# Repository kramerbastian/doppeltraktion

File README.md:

# *doppeltraktion*

Doppeltraktion (German for double heading — that's when two locomotives pull together on a train) is the world's most intuitive model railway throttle. It has ≈6x fewer buttons and switches than market competitors, such as the Uhlenbrock Intellibox II. It connects to your model railroad using LCC or to your computer via USB to control software such as RocRail or JMRI*¹ and can control two locomotives simultaneously. <br>
<sub>*¹ not yet implemented</sub>

### Functions

### What is LCC?

LCC is a relatively new standard by the NMRA to control devices using a CAN bus. It's completely free and open-source, unlike alternatives like LocoNet, which comes with a pretty hefty licensing fee for device manufacturers.

### Motivation

I've been building on my model railway from an early age. As time progressed, the electronics and operations became so complicated that nobody else could really control it. That's why I always wanted to build a physical throttle that's not dependent on external computers or phones. Everything should be ready to use when you turn on the power. Of course, there are alternatives from big manufacturers, such as the mentioned Intellibox or the ESU ECoS, but these devices are very expensive (500€+) and aren't compatible with my DIY DCCEX base station.

### Design

It might seem a bit unusual to have five PCBs for this relatively small project, but to keep PCB costs low (by being under 100x100mm), I decided to split the covers (aluminum PCBs) and those boards where the switches, LEDs, and potentiometers mount. The PCBs on the side are identical. Everything is connected to a custom, small control board, which houses the ESP32 as well as all the CAN circuitry (for LCC).

By also splitting the base into two parts, everything should fit on the 180x180mm build plate of the A1 mini.

The plates (that‘s where the switches mount mechanically) use a sandwich design (top plate - bottom plate - PCB) to avoid having to use supports and ensure dimensional accuracy for mounting the switches.

I couldn’t find a good CAD model or accurate dimensions for the 16mm selector knob, so there’s a hole in the cover and the plates beneath it. The cutout size should be correct. I just need to verify the depth and maybe adjust the top side plate once the switch arrives.

#### Designed Parts

| Name                                                  | Image                                                                                                                                     | File                                                  | Quantity  |
|-------------------------------------------------------|-------------------------------------------------------------------------------------------------------------------------------------------|-------------------------------------------------------|-----------|
| Top center plate                                      |          | [STL](./production/3d/top_center_plate.stl)           | 1         |
| Bottom center plate                                   |    | [STL](./production/3d/bottom_center_plate.stl)        | 1         |
| Top side plate                                        |              | [STL](./production/3d/top_side_plate.stl)             | 2         |
| Bottom side plate                                     |        | [STL](./production/3d/bottom_side_plate.stl)          | 2         |
| Top left base                                         |                | [STL](./production/3d/top_base_left.stl.stl)          | 1         |
| Top right base                                        |             | [STL](./production/3d/top_base_right.stl)             | 1         |
| Bottom left base                                      |          | [STL](./production/3d/bottom_base_left.stl.stl)       | 1         |
| Bottom right base                                     |           | [STL](./production/3d/bottom_base_right.stl)          | 1         |
| Bottom cover                                          |             | [STL](./production/3d/bottom_cover.stl)               | 2         |
| Light guide <br> (print the last layer in white PLA)  |               | [STL](./production/3d/light_guide.stl)          | 7         |
| Knob                                                  |                      | [STL](./production/3d/knob.stl)                    | 1         |
| Mounting PCB side                                     |         | [Gerber](./production/pcbs/side.zip)                  | 2         |
| Mounting PCB center                                   |       | [Gerber](./production/pcbs/center.zip)                | 1         |
| Control PCB                                           |               | [Gerber](./production/pcbs/control.zip)               | 1         |
| Center cover                                          |              | [Gerber](./production/pcbs/cover_center.zip)          | 1         |
| Side cover                                            |                | [Gerber](./production/pcbs/cover_side.zip)            | 2         |

### Assembly

1. Print all necessary parts: 2x [top side plate](./production/3d/top_side_plate.stl), 2x [bottom side plate](./production/3d/bottom_side_plate.stl), 1x [top center plate](./production/3d/top_center_plate.stl), 1x [bottom center plate](./production/3d/bottom_center_plate.stl), 1x [top left base](./production/3d/top_base_left.stl), 1x [top right base](./production/3d/top_base_right.stl), 1x [bottom left base](./production/3d/bottom_base_left.stl), 1x [bottom right base](./production/3d/bottom_base_right.stl), 1x [bottom left cover](./production/3d/bottom_cover_left.stl), 1x [bottom right cover](./production/3d/bottom_cover_right.stl). (I know these names are awful, but I couldn‘t come up with better ones.)

2. Insert the heat-set inserts into their respective holes.

3. Mount all the PCBs and solder the switches in place.

4. You can now secure the plates onto the top base. With the control board mounted on the bottom base, it can also be secured to the top base.

5. Now is the time to run the wires from the modules (2x side, 1x center) and the display to the control board. Also, wire up the selector knob to the WAGO terminals and ground.

6. The final step is to screw both the top cover (the aluminium one) and the bottom cover onto the construction.

### BOM

|Part                     |Manufacturer               |Product                             |Quantity|Price each|Total Price|Link                                                                                                                                            |
|-------------------------|---------------------------|------------------------------------|--------|----------|-----------|------------------------------------------------------------------------------------------------------------------------------------------------|
|Inserts                  |YMAX                       |Brass Threaded Insert Nut Kit       |1       | $1.460   | $1.46     | [Link](https://www.aliexpress.com/item/1005006472962973.html)                                                                                  |
|Display                  |EstarDyn                   |12864-06D                           |1       | $6.250   | $6.25     |[Link](https://www.aliexpress.com/item/1005006160620381.html)                                                                                   |
|Rotary Knob              |Sweideer                   |LA-155C                             |1       | $2.630   | $2.63     |[Link](https://www.aliexpress.com/item/1005007495183351.html)                                                                                   |
|Switches                 |-                          |10 Pieces Keyboard Replacement Parts|1       | $1.590   | $1.59     |[Link](https://www.aliexpress.com/item/1005004341695529.html)                                                                                   |
|Keycaps                  |-                          |B0KA 20PCs PBT Blank                |1       | $4.470   | $4.47     |[Link](https://www.aliexpress.com/item/1005004525231272.html)                                                                                   |
|M2x5 12x                 |SCREWHOME                  |50pcs M2x5mm ULTRATHIN              |1       | $1.460   | $1.46     |[Link](https://www.aliexpress.com/item/1005005070119421.html)                                                                                   |
|M2x10 4x                 |LIYA                       |50pcs M2x10mm                       |1       | $1.560   | $1.56     |[Link](https://www.aliexpress.com/item/32810872544.html)                                                                                        |
|M3x20 2x                 |LIYA                       |50pcs M3x20mm                       |1       | $2.760   | $2.76     |[Link](https://www.aliexpress.com/item/32810872544.html)                                                                                        |
|M3x8 8x                  |LIYA                       |50pcs M3x8mm                        |1       | $1.730   | $1.73     |[Link](https://www.aliexpress.com/item/32810872544.html)                                                                                        |
|M3x8 Countersunk 8x      |ZONST                      |50pcs M3x8mm Countersunk            |1       | $1.810   | $1.81     |[Link](https://www.aliexpress.com/item/1005002333132596.html)                                                                                   |
|M3x12 12x                |LIYA                       |50pcs M3x12mm                       |1       | $2.060   | $2.06     |[Link](https://www.aliexpress.com/item/32810872544.html)                                                                                        |
|M3x10 5x                 |LIYA                       |50pcs M3x10mm                       |1       | $1.940   | $1.94     |[Link](https://www.aliexpress.com/item/32810872544.html)                                                                                        |
|ESP32-S3                 |EXPRESSIF                  |ESP32-S3-WROOM-1U-N16R2             |1       | $5.660   | $5.66     |[Link](https://lcsc.com/product-detail/WiFi-Modules_ESPRESSIF-ESP32-S3-WROOM-1U-N16R8_C3013946.html)                                            |
|LDO                      |Advanced Monolithic Systems|AMS1117-3.3                         |5       | $0.170   | $0.85     |[Link](https://lcsc.com/product-detail/Voltage-Regulators-Linear-Low-Drop-Out-LDO-Regulators_Advanced-Monolithic-Systems-AMS1117-3-3_C6186.html)|
|CAN transceiver          |NXP                        |TJA1051T,118                        |1       | $0.960   | $0.96     |[Link](https://lcsc.com/product-detail/CAN-Transceivers_NXP-TJA1051T-118_C18387.html)                                                           |
|I/O expander             |HGSEMI                     |PCF8574T/TR                         |1       | $0.790   | $0.79     |[Link](https://lcsc.com/product-detail/I-O-Expanders_HGSEMI-PCF8574T-TR_C2987288.html)                                                          |
|4 pin connector          |JST                        |B4B-PH-K-S(LF)(SN)                  |10      | $0.041   | $0.41     |[Link](https://lcsc.com/product-detail/Wire-To-Board-Connector_JST-B4B-PH-K-S-LF-SN_C131334.html)                                               |
|6 pin connector          |JST                        |B6B-PH-K-S(LF)(SN)                  |10      | $0.067   | $0.67     |[Link](https://lcsc.com/product-detail/Wire-To-Board-Connector_JST-B6B-PH-K-S-LF-SN_C131342.html)                                               |
|9 pin connector          |JST                        |B9B-PH-K-S(LF)(SN)                  |5       | $0.051   | $0.26     |[Link](https://lcsc.com/product-detail/Wire-To-Board-Connector_JST-B9B-PH-K-S-LF-SN_C157968.html)                                               |
|4 pin connector housing  |JST                        |PHR-4                               |50      | $0.016   | $0.79     |[Link](https://lcsc.com/product-detail/Housings-Wire-To-Board-Wire-To-Wire_JST-PHR-4_C111514.html)                                              |
|6 pin connector housing  |JST                        |PHR-6                               |20      | $0.020   | $0.40     |[Link](https://lcsc.com/product-detail/Housings-Wire-To-Board-Wire-To-Wire_JST-PHR-6_C157952.html)                                              |
|9 pin connector housing  |JST                        |PHR-9                               |20      | $0.036   | $0.72     |[Link](https://lcsc.com/product-detail/Housings-Wire-To-Board-Wire-To-Wire_JST-PHR-9_C157949.html)                                              |
|Connector contact        |JST                        |SPH-002T-P0.5S                      |100     | $0.008   | $0.80     |[Link](https://lcsc.com/product-detail/Housing-Contact_JST-SPH-002T-P0-5S_C111515.html)                                                         |
|USB-B port               |TE Connectivity            |292304-1                            |1       | $0.470   | $0.47     |[Link](https://lcsc.com/product-detail/USB-Connectors_TE-Connectivity-292304-1_C86462.html)                                                     |
|100uF capacitors         |Rubycon                    |35ZLH100MEFC6.3X11                  |10      | $0.059   | $0.59     |[Link](https://lcsc.com/product-detail/Aluminum-Electrolytic-Capacitors-Leaded_Rubycon-35ZLH100MEFC6-3X11_C109392.html)                         |
|100nF capacitors         |Samsung Electro-Mechanics  |CL31B104KBCNNNC                     |20      | $0.137   | $2.74     |[Link](https://lcsc.com/product-detail/Multilayer-Ceramic-Capacitors-MLCC-SMD-SMT_Samsung-Electro-Mechanics-CL31B104KBCNNNC_C24497.html)        |
|10kOhm resistors         |YAGEO                      |RC1206FR-0710KL                     |100     | $0.004   | $0.37     |[Link](https://lcsc.com/product-detail/Chip-Resistor-Surface-Mount_YAGEO-RC1206FR-0710KL_C132649.html)                                          |
|Sliding potentiometers   |ALPSALPINE                 |RS6011YA600M                        |2       | $1.451   | $2.90     |[Link](https://lcsc.com/product-detail/Potentiometers-Variable-Resistors_ALPSALPINE-RS6011YA600M_C470623.html)                                  |
|RGB LEDs                 |XINGLIGHT                  |XL-5050RGBC-WS2812B                 |20      | $0.049   | $0.98     |[Link](https://lcsc.com/product-detail/RGB-LEDs-Built-in-IC_XINGLIGHT-XL-5050RGBC-WS2812B_C2843785.html)                                        |
|RJ45 port - existing     |Phoenix Contact            |1337243                             |2       | -        | -         |[Link](https://www.phoenixcontact.com/en-pc/products/rj45-pcb-connectors-cuc-sp-j1st-a-r4lt-thr-led-1337243)                                    |
|WAGO terminals - existing|WAGO                       |2601-3105                           |2       | -        | -         |[Link](https://www.wago.com/de/leiterplattenanschluss/leiterplattenklemme/p/2601-3105)                                                          |
|Slide switch - existing  |XKB Connection             |SS13E05L2                           |1       | -        | -         |[Link](https://lcsc.com/product-detail/Slide-Switches_XKB-Connection-SS13E05L2_C2884809.html)                                                   |
|Control PCB              |JLCPCB                     |5x FR4 PCB                          |1       | $1.720   | $1.72     |                                                                                                                                                |
|Side PCB                 |JLCPCB                     |5x FR4 PCB                          |1       | $3.440   | $3.44     |                                                                                                                                                |
|Center PCB               |JLCPCB                     |5x FR4 PCB                          |1       | $3.440   | $3.44     |                                                                                                                                                |
|Center cover             |JLCPCB                     |5x Aluminum PCB                     |1       | $3.390   | $3.39     |                                                                                                                                                |
|Cover                    |JLCPCB                     |5x Aluminum PCB                     |1       | $3.390   | $3.39     |                                                                                                                                                |
|JLCPCB shipping and taxes|                           |                                    |1       | $11.020  | $11.02    |                                                                                                                                                |
|LCSC shipping            |                           |                                    |1       | $9.420   | $9.42     |                                                                                                                                                |
|**Total**                |                           |                                    |        |          | **$85.90**|                                                                                                                                                |

#### Opening the CAD File
This project was built in multiple design files, which can‘t be combined without compromising the whole model. To import the CAD model, open Fusion 360, **create a new folder** and upload the [.f3z](./hardware/cad/Throttle.f3z) file into this created folder. You can now open the `Throttle` design file.

-------
<div style="display: flex; justify-items: center; flex-direction: row; gap: 4px; font-size: 12px;">
Supported by

</div>

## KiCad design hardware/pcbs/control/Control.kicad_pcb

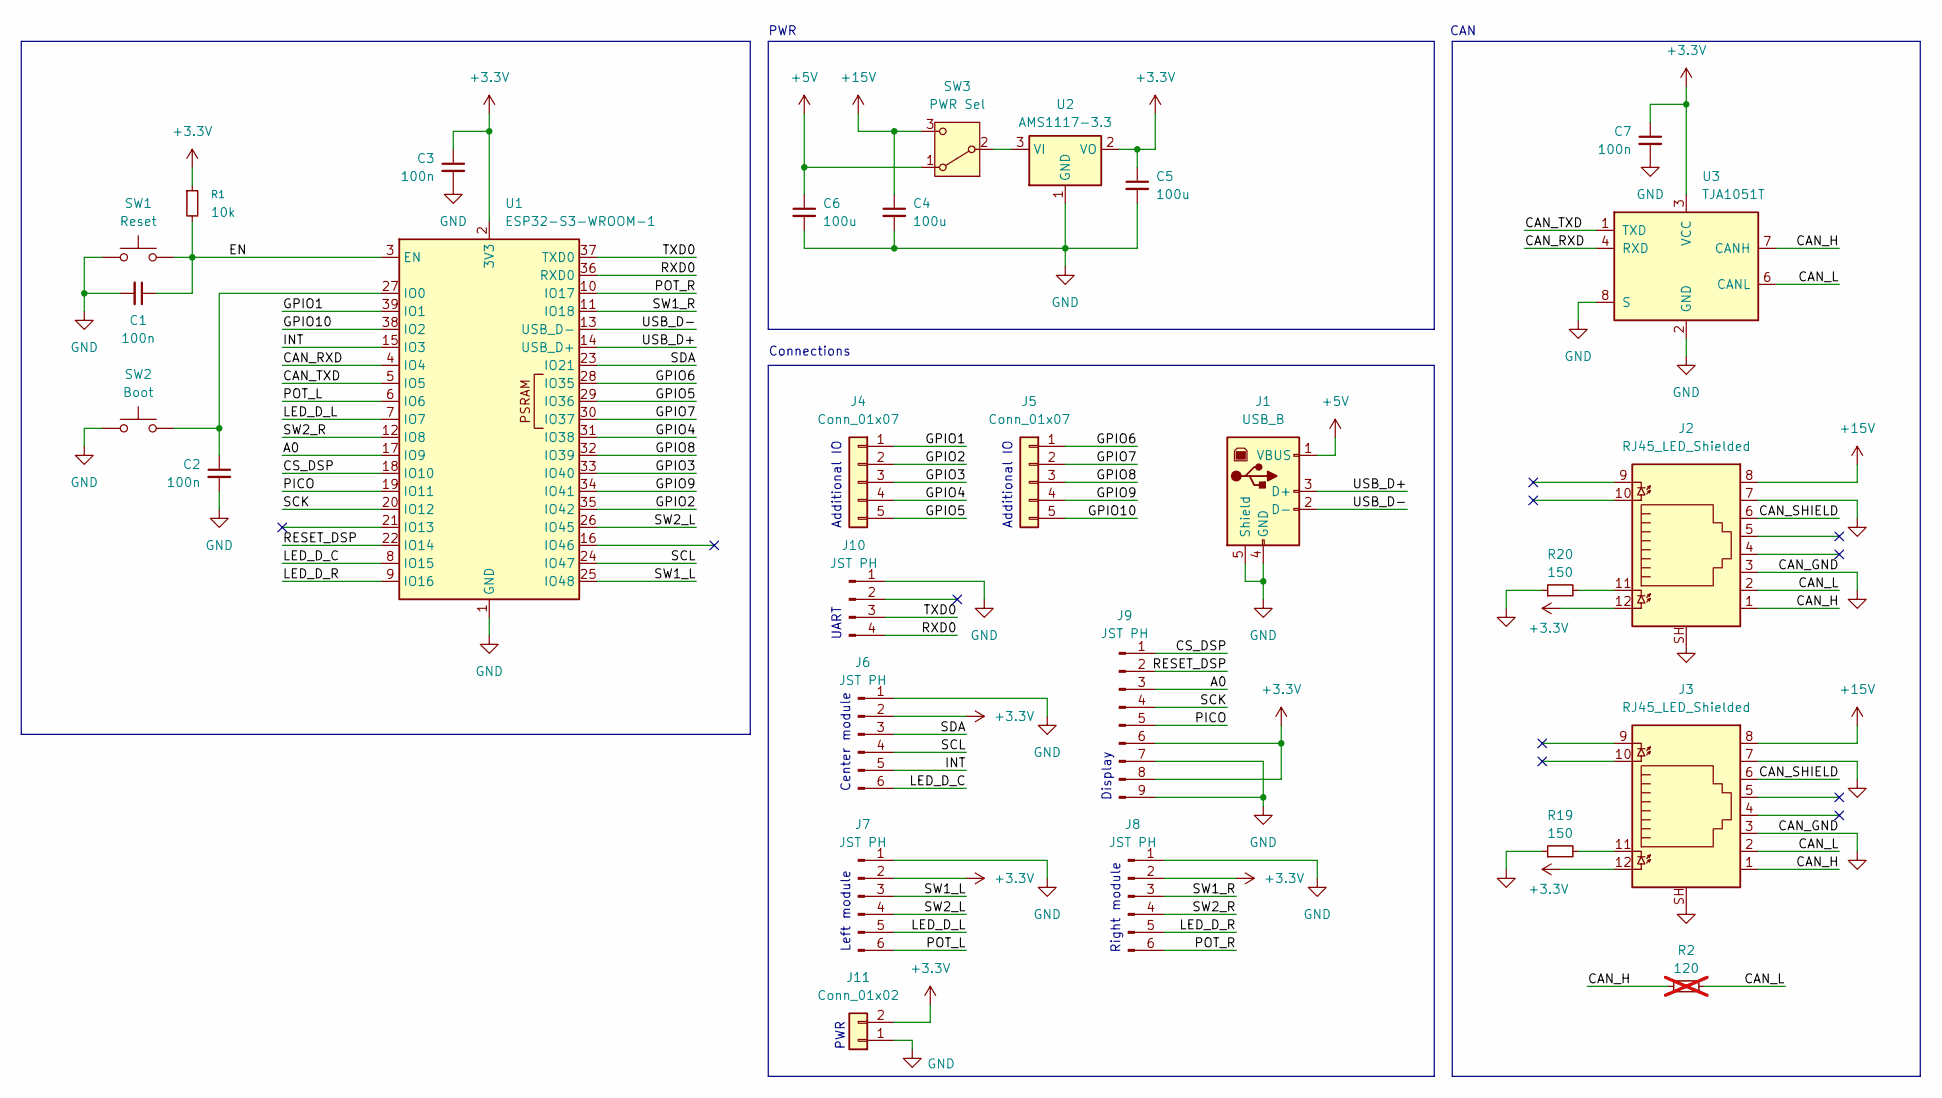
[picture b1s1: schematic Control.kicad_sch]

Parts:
C1, C2, C3, C7: 100n; C_1206_3216Metric
C4, C5, C6: 100u; C_Radial_D6.3mm_H7.0mm_P2.50mm
J1: USB_B; TE Connectivity_292304_USB_B
J2, J3: RJ45_LED_Shielded; PHOENIX_1337243; LCSC C386757
J4, J5: Conn_01x07; TerminalBlock_WAGO_2601-3105_1x05_P3.50mm_Vertical
J6, J7, J8: JST PH; JST_PH_B6B-PH-K_1x06_P2.00mm_Vertical
J9: JST PH; JST_PH_B9B-PH-K_1x09_P2.00mm_Vertical
J10: JST PH; JST_PH_B4B-PH-K_1x04_P2.00mm_Vertical
J11: Conn_01x02; TerminalBlock_WAGO_2601-3102_1x02_P3.50mm_Vertical
R1: 10k; R_1206_3216Metric
R2: 120; R_Axial_DIN0207_L6.3mm_D2.5mm_P7.62mm_Horizontal; not fitted
R19, R20: 150; R_1206_3216Metric; LCSC C2907432
SW1: Reset; SW-SMD_L3.9-W3.0-P4.45
SW2: Boot; SW-SMD_L3.9-W3.0-P4.45
SW3: PWR Sel; SW-TH_SS13E05LX
U1: ESP32-S3-WROOM-1; ESP32-S3-WROOM-1U
U2: AMS1117-3.3; SOT-223-3_TabPin2
U3: TJA1051T; SOIC-8_3.9x4.9mm_P1.27mm

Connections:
+3.3V: C3.1, C5.1, C7.1, J2.12, J3.12, J6.2, J7.2, J8.2, J9.6, J9.8, J11.2, R1.1, U1.2 (3V3), U2.2 (VO), U3.3 (VCC)
+5V: C6.1, J1.1 (VBUS), SW3.1 (A)
+15V: C4.1, J2.8, J3.8, SW3.3 (C)
/A0: J9.3, U1.17 (IO9)
/CAN_H: J2.1, J3.1, R2.1, U3.7 (CANH)
/CAN_L: J2.2, J3.2, R2.2, U3.6 (CANL)
/CAN_RXD: U1.4 (IO4), U3.4 (RXD)
/CAN_SHIELD: J2.6, J3.6
/CAN_TXD: U1.5 (IO5), U3.1 (TXD)
/CS_DSP: J9.1, U1.18 (IO10)
/EN: C1.1, R1.2, SW1.2, U1.3 (EN)
/GPIO1: J4.1, U1.39 (IO1)
/GPIO2: J4.2, U1.35 (IO42)
/GPIO3: J4.3, U1.33 (IO40)
/GPIO4: J4.4, U1.31 (IO38)
/GPIO5: J4.5, U1.29 (IO36)
/GPIO6: J5.1, U1.28 (IO35)
/GPIO7: J5.2, U1.30 (IO37)
/GPIO8: J5.3, U1.32 (IO39)
/GPIO9: J5.4, U1.34 (IO41)
/GPIO10: J5.5, U1.38 (IO2)
/INT: J6.5, U1.15 (IO3)
/LED_D_C: J6.6, U1.8 (IO15)
/LED_D_L: J7.5, U1.7 (IO7)
/LED_D_R: J8.5, U1.9 (IO16)
/PICO: J9.5, U1.19 (IO11)
/POT_L: J7.6, U1.6 (IO6)
/POT_R: J8.6, U1.10 (IO17)
/RESET_DSP: J9.2, U1.22 (IO14)
/RXD0: J10.4, U1.36 (RXD0)
/SCK: J9.4, U1.20 (IO12)
/SCL: J6.4, U1.24 (IO47)
/SDA: J6.3, U1.23 (IO21)
/SW1_L: J7.3, U1.25 (IO48)
/SW1_R: J8.3, U1.11 (IO18)
/SW2_L: J7.4, U1.26 (IO45)
/SW2_R: J8.4, U1.12 (IO8)
/TXD0: J10.3, U1.37 (TXD0)
/USB_D+: J1.3 (D+), U1.14 (USB_D+)
/USB_D-: J1.2 (D-), U1.13 (USB_D-)
GND: C1.2, C2.2, C3.2, C4.2, C5.2, C6.2, C7.2, J1.4 (GND), J1.5 (Shield), J2.3, J2.7, J2.SH, J3.3, J3.7, J3.SH, J6.1, J7.1, J8.1, J9.7, J9.9, J10.1, J11.1, R19.1, R20.1, SW1.1, SW2.1, U1.1 (GND), U1.40 (GND), U1.41 (GND), U2.1 (GND), U3.2 (GND), U3.8 (S)
unnamed: J2.11, R20.2
unnamed: J3.11, R19.2
unnamed: SW3.2 (B), U2.3 (VI)
unnamed: C2.1, SW2.2, U1.27 (IO0)

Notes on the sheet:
UART
Additional IO
Center module
CAN
PWR
Left module
Display
Right module
Connections

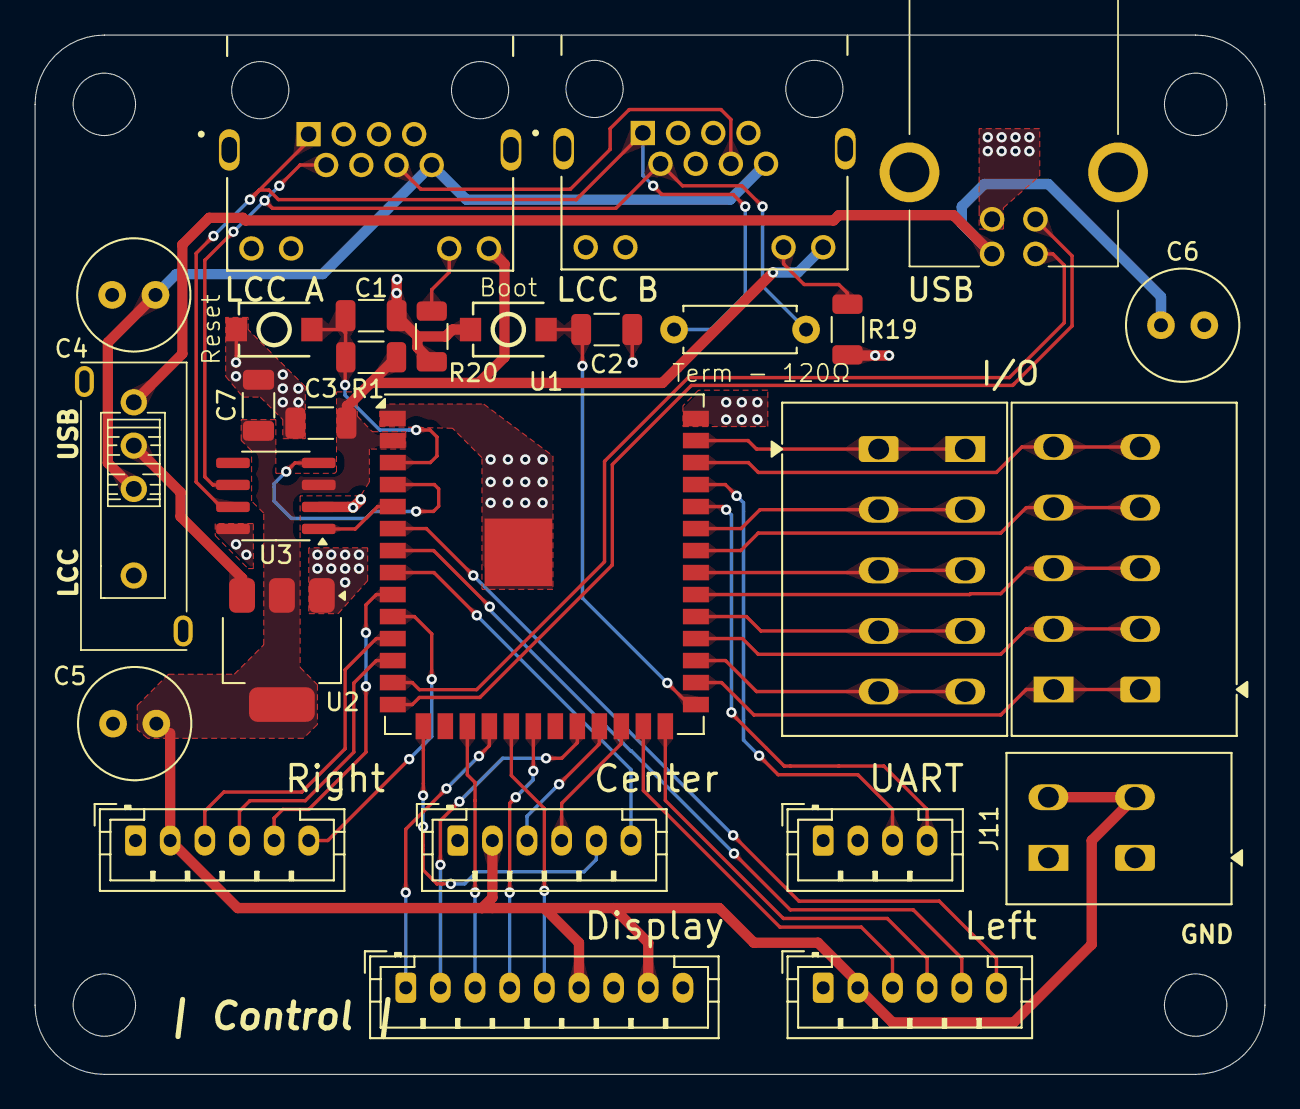
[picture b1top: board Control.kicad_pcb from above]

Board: 2 copper layers, 71.0 x 60.0 mm, 28 parts (0 on the bottom side), 45 nets.

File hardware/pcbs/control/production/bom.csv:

Designator,Footprint,Quantity,Value,LCSC Part #
"C1, C2, C3, C7",1206,4,100n,
"C4, C5, C6",C_Radial_D6.3mm_H7.0mm_P2.50mm,3,100u,
J1,TE Connectivity_292304_USB_B,1,USB_B,
J10,JST_PH_B4B-PH-K_1x04_P2.00mm_Vertical,1,JST PH,
J11,TerminalBlock_WAGO_2601-3102_1x02_P3.50mm_Vertical,1,Conn_01x02,
"J2, J3",PHOENIX_1337243,2,RJ45_LED_Shielded,C386757
"J4, J5",TerminalBlock_WAGO_2601-3105_1x05_P3.50mm_Vertical,2,Conn_01x07,
"J6, J7, J8",JST_PH_B6B-PH-K_1x06_P2.00mm_Vertical,3,JST PH,
J9,JST_PH_B9B-PH-K_1x09_P2.00mm_Vertical,1,JST PH,
R1,1206,1,10k,
"R19, R20",1206,2,150,C2907432
SW1,SW-SMD_L3.9-W3.0-P4.45,1,Reset,
SW2,SW-SMD_L3.9-W3.0-P4.45,1,Boot,
SW3,SW-TH_SS13E05LX,1,PWR Sel,
U1,ESP32-S3-WROOM-1U,1,ESP32-S3-WROOM-1,
U2,SOT-223-3_TabPin2,1,AMS1117-3.3,
U3,SOIC-8_3.9x4.9mm_P1.27mm,1,TJA1051T,

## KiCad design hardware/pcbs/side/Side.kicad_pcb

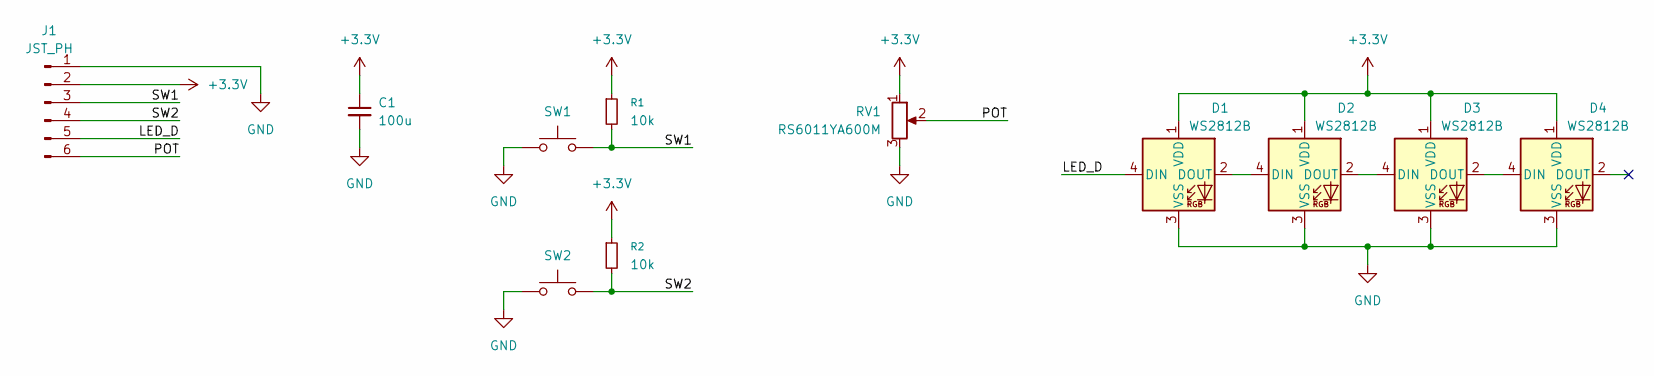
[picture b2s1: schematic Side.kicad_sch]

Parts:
C1: 100u; C_Radial_D6.3mm_H7.0mm_P2.50mm
D1, D2, D3, D4: WS2812B; LED_WS2812B_PLCC4_5.0x5.0mm_P3.2mm
J1: JST_PH; JST_PH_B6B-PH-K_1x06_P2.00mm_Vertical
R1, R2: 10k; R_1206_3216Metric
RV1: RS6011YA600M
SW1, SW2: SW_Push; SW_Cherry_MX_1.00u_PCB

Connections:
+3.3V: C1.1, D1.1 (VDD), D2.1 (VDD), D3.1 (VDD), D4.1 (VDD), J1.2, R1.1, R2.1, RV1.1
/LED_D: D1.4 (DIN), J1.5
/POT: J1.6, RV1.2
/SW1: J1.3, R1.2, SW1.2
/SW2: J1.4, R2.2, SW2.2
GND: C1.2, D1.3 (VSS), D2.3 (VSS), D3.3 (VSS), D4.3 (VSS), J1.1, RV1.3, SW1.1, SW2.1
unnamed: D1.2 (DOUT), D2.4 (DIN)
unnamed: D2.2 (DOUT), D3.4 (DIN)
unnamed: D3.2 (DOUT), D4.4 (DIN)

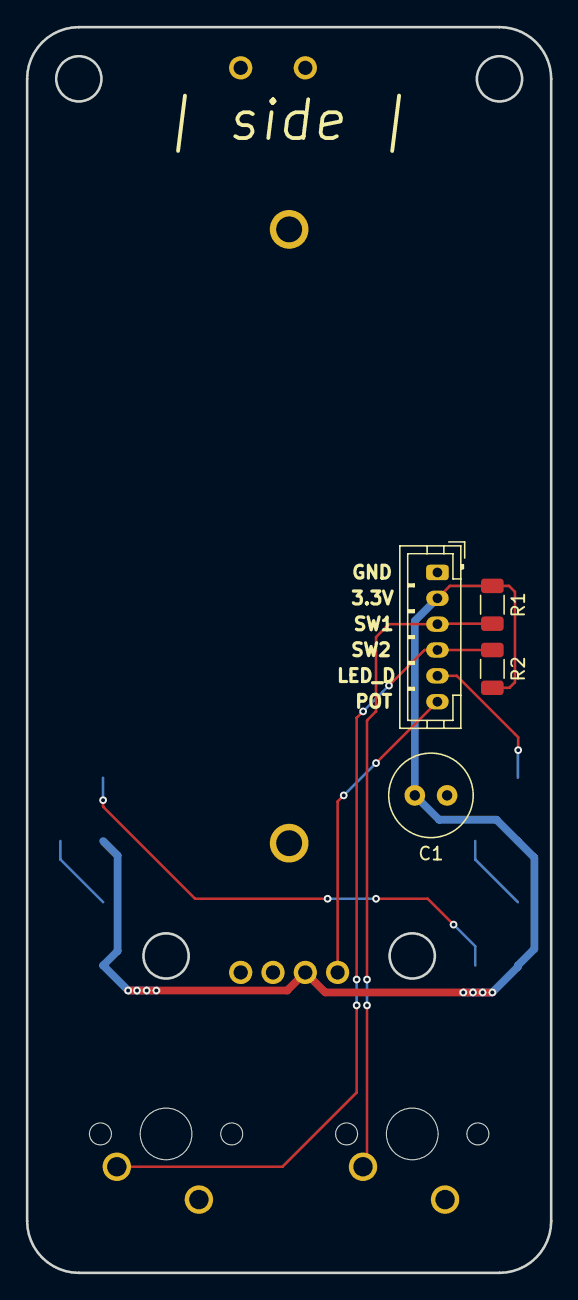
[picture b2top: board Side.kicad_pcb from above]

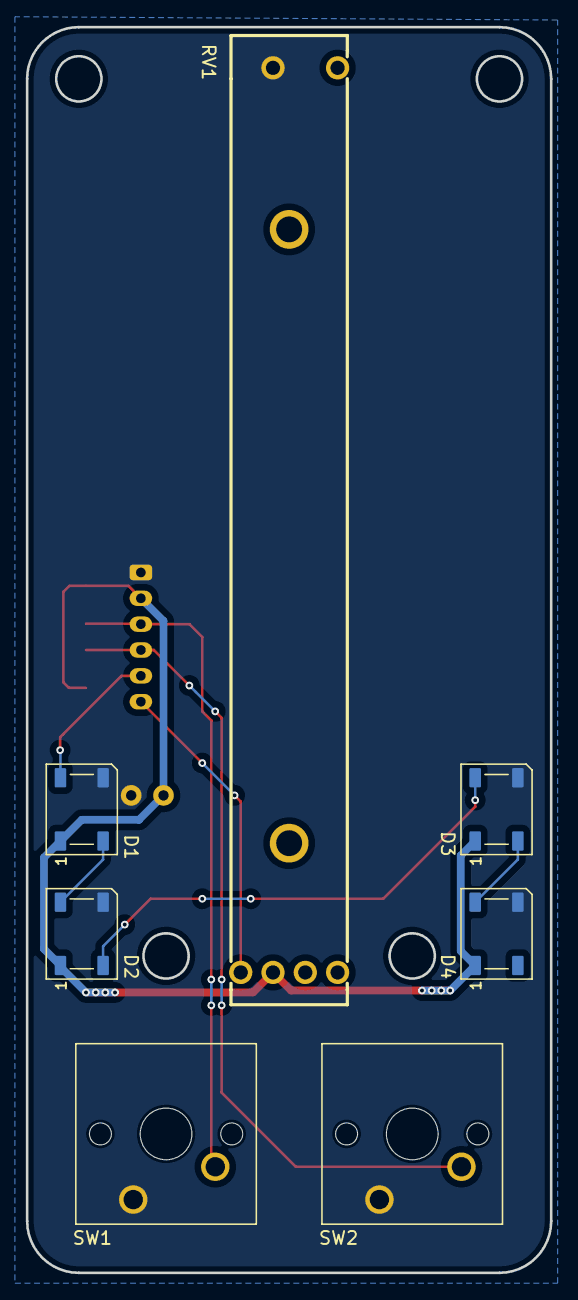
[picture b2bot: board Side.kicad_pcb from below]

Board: 2 copper layers, 40.6 x 96.4 mm, 11 parts (7 on the bottom side), 9 nets.

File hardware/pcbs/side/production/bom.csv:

Designator,Footprint,Quantity,Value,LCSC Part #
C1,C_Radial_D6.3mm_H7.0mm_P2.50mm,1,100u,
"D1, D2, D3, D4",LED_WS2812B_PLCC4_5.0x5.0mm_P3.2mm,4,WS2812B,
J1,JST_PH_B6B-PH-K_1x06_P2.00mm_Vertical,1,JST_PH,
"R1, R2",1206,2,10k,
RV1,RS6011YA600M,1,RS6011YA600M,
"SW1, SW2",SW_Cherry_MX_1.00u_PCB,2,SW_Push,

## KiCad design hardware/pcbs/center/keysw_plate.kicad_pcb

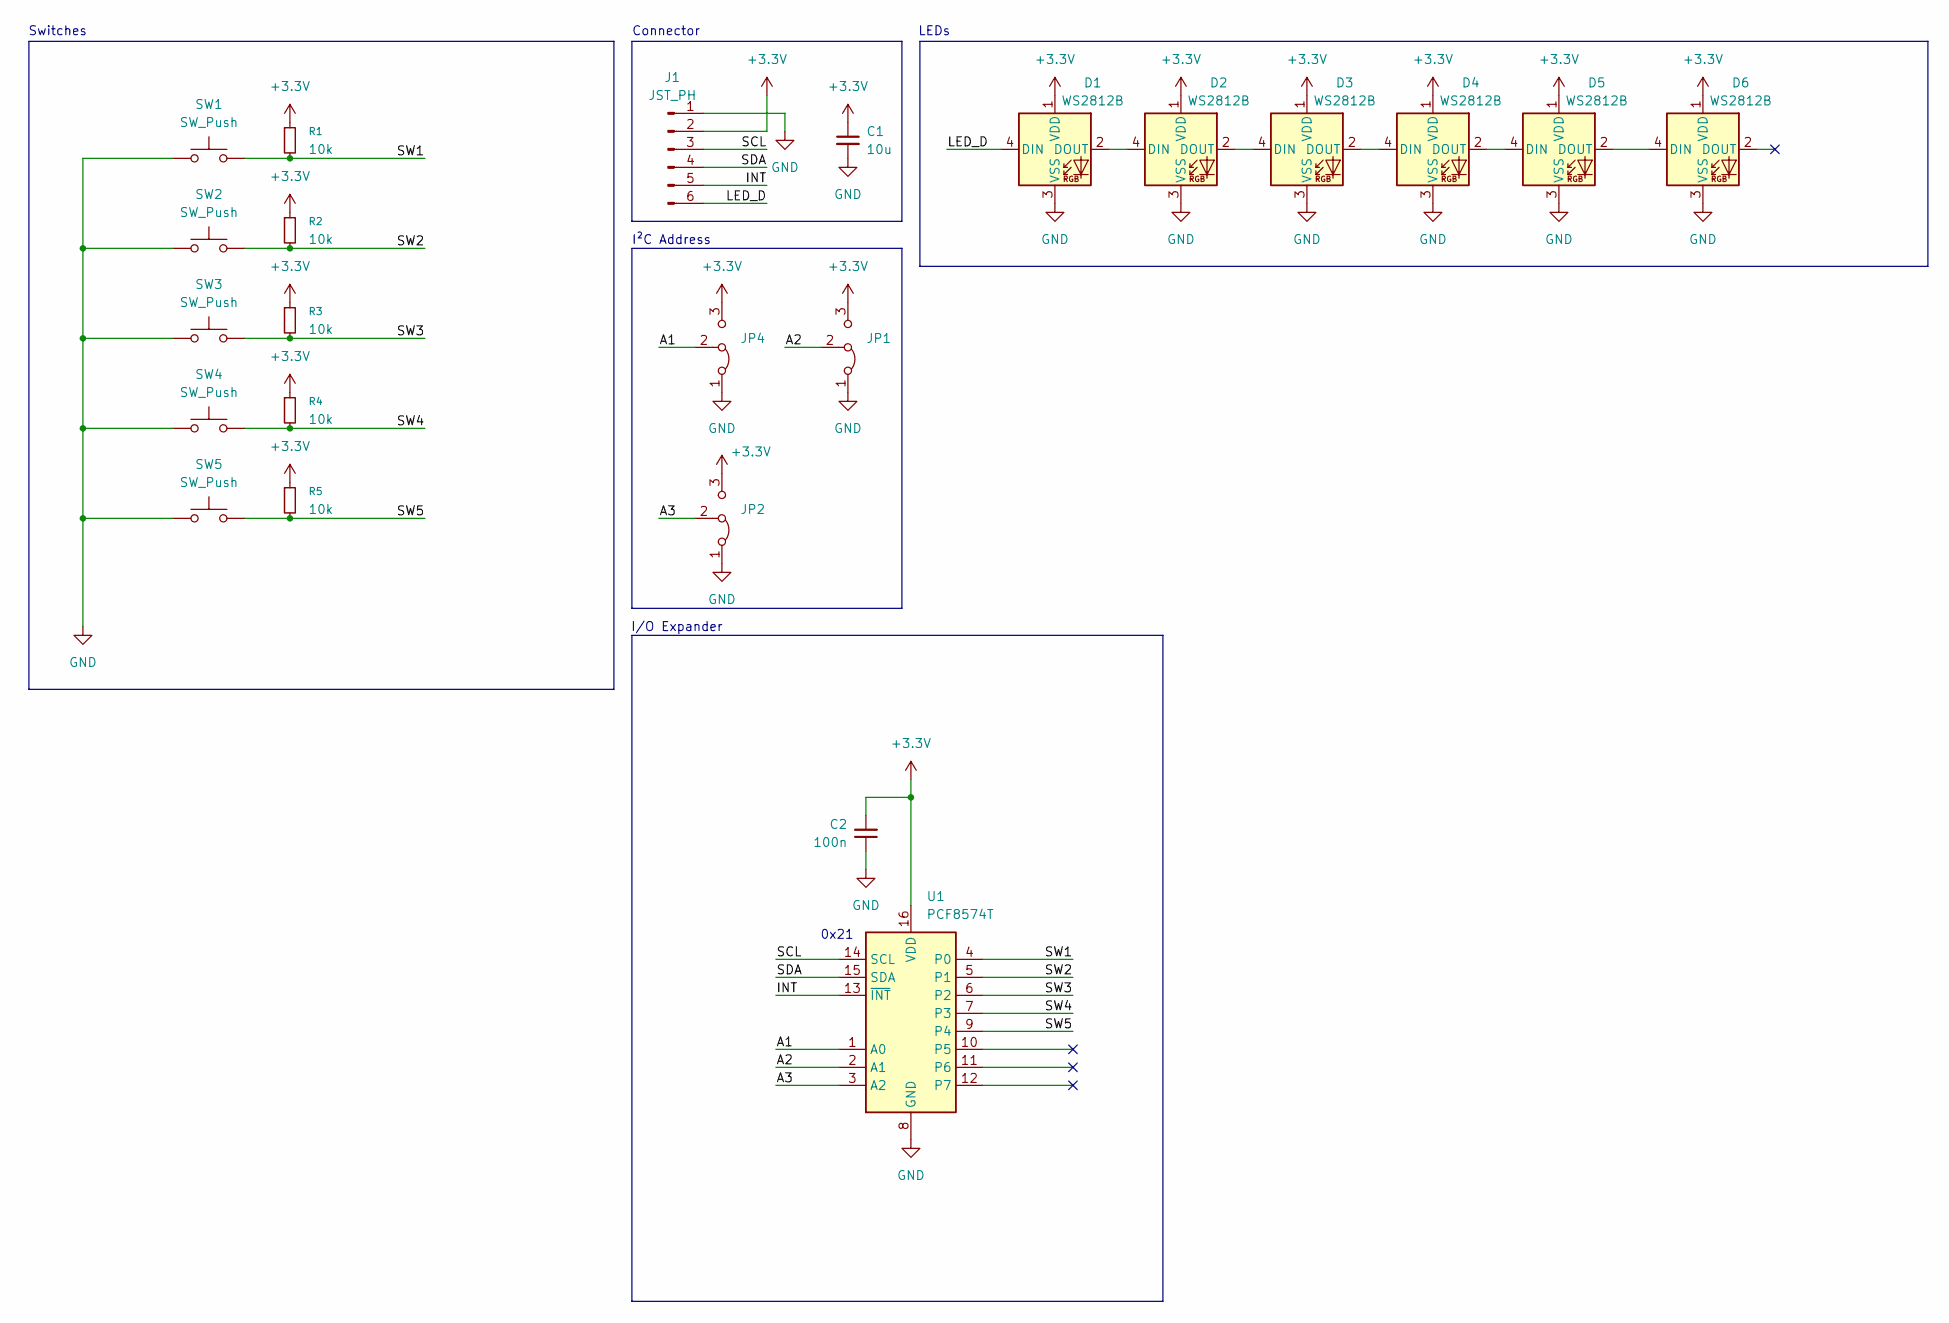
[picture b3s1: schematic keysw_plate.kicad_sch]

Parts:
C1: 10u; C_Radial_D6.3mm_H11.0mm_P2.50mm
C2: 100n; C_1206_3216Metric
D1, D2, D3, D4, D5, D6: WS2812B; LED_WS2812B_PLCC4_5.0x5.0mm_P3.2mm
J1: JST_PH; JST_PH_B6B-PH-K_1x06_P2.00mm_Vertical
JP1, JP2, JP4: Jumper_3_Bridged12; SolderJumper-3_P1.3mm_Bridged2Bar12_Pad1.0x1.5mm
R1, R2, R3, R4, R5: 10k; R_1206_3216Metric
SW1, SW2, SW3, SW4, SW5: SW_Push; SW_Cherry_MX_1.00u_PCB
U1: PCF8574T; SOIC-16W_7.5x10.3mm_P1.27mm

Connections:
+3.3V: C1.1, C2.2, D1.1 (VDD), D2.1 (VDD), D3.1 (VDD), D4.1 (VDD), D5.1 (VDD), D6.1 (VDD), J1.2, JP1.3 (B), JP2.3 (B), JP4.3 (B), R1.1, R2.1, R3.1, R4.1, R5.1, U1.16 (VDD)
/A1: JP4.2 (C), U1.1 (A0)
/A2: JP1.2 (C), U1.2 (A1)
/A3: JP2.2 (C), U1.3 (A2)
/INT: J1.5, U1.13 (~INT)
/LED_D: D1.4 (DIN), J1.6
/SCL: J1.3, U1.14 (SCL)
/SDA: J1.4, U1.15 (SDA)
/SW1: R1.2, SW1.2, U1.4 (P0)
/SW2: R2.2, SW2.2, U1.5 (P1)
/SW3: R3.2, SW3.2, U1.6 (P2)
/SW4: R4.2, SW4.2, U1.7 (P3)
/SW5: R5.2, SW5.2, U1.9 (P4)
GND: C1.2, C2.1, D1.3 (VSS), D2.3 (VSS), D3.3 (VSS), D4.3 (VSS), D5.3 (VSS), D6.3 (VSS), J1.1, JP1.1 (A), JP2.1 (A), JP4.1 (A), SW1.1, SW2.1, SW3.1, SW4.1, SW5.1, U1.8 (GND)
unnamed: D1.2 (DOUT), D2.4 (DIN)
unnamed: D2.2 (DOUT), D3.4 (DIN)
unnamed: D3.2 (DOUT), D4.4 (DIN)
unnamed: D4.2 (DOUT), D5.4 (DIN)
unnamed: D5.2 (DOUT), D6.4 (DIN)

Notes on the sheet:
0x21
I/O Expander
LEDs
I²C Address
Connector
Switches

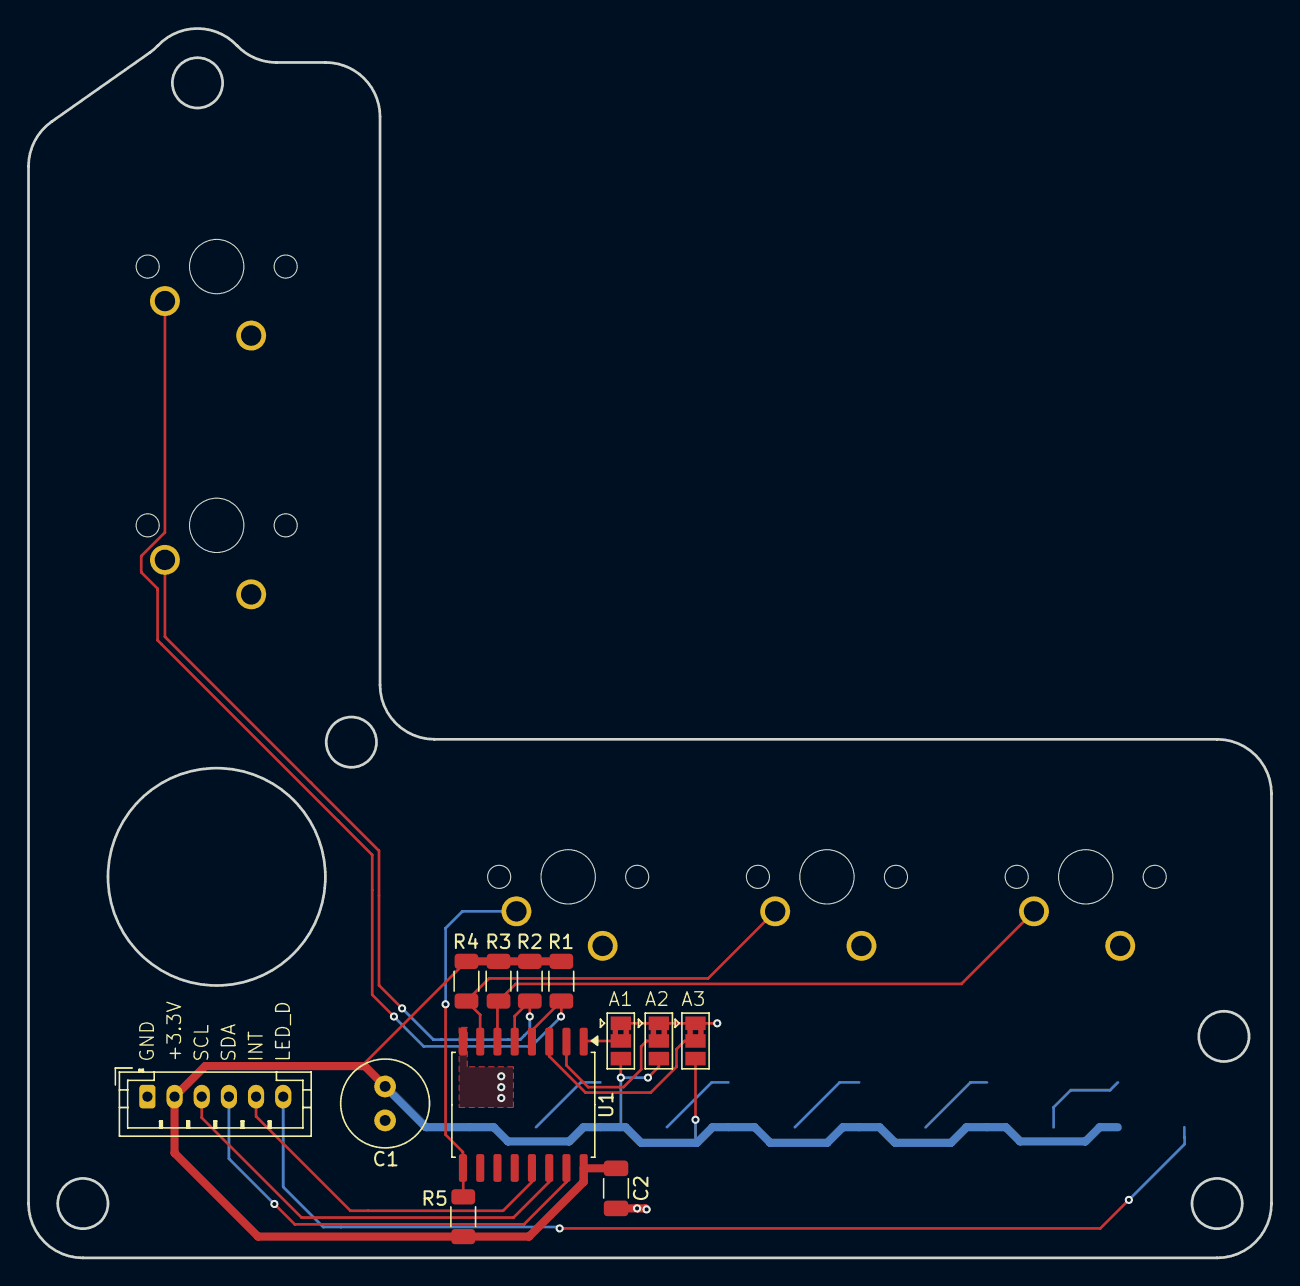
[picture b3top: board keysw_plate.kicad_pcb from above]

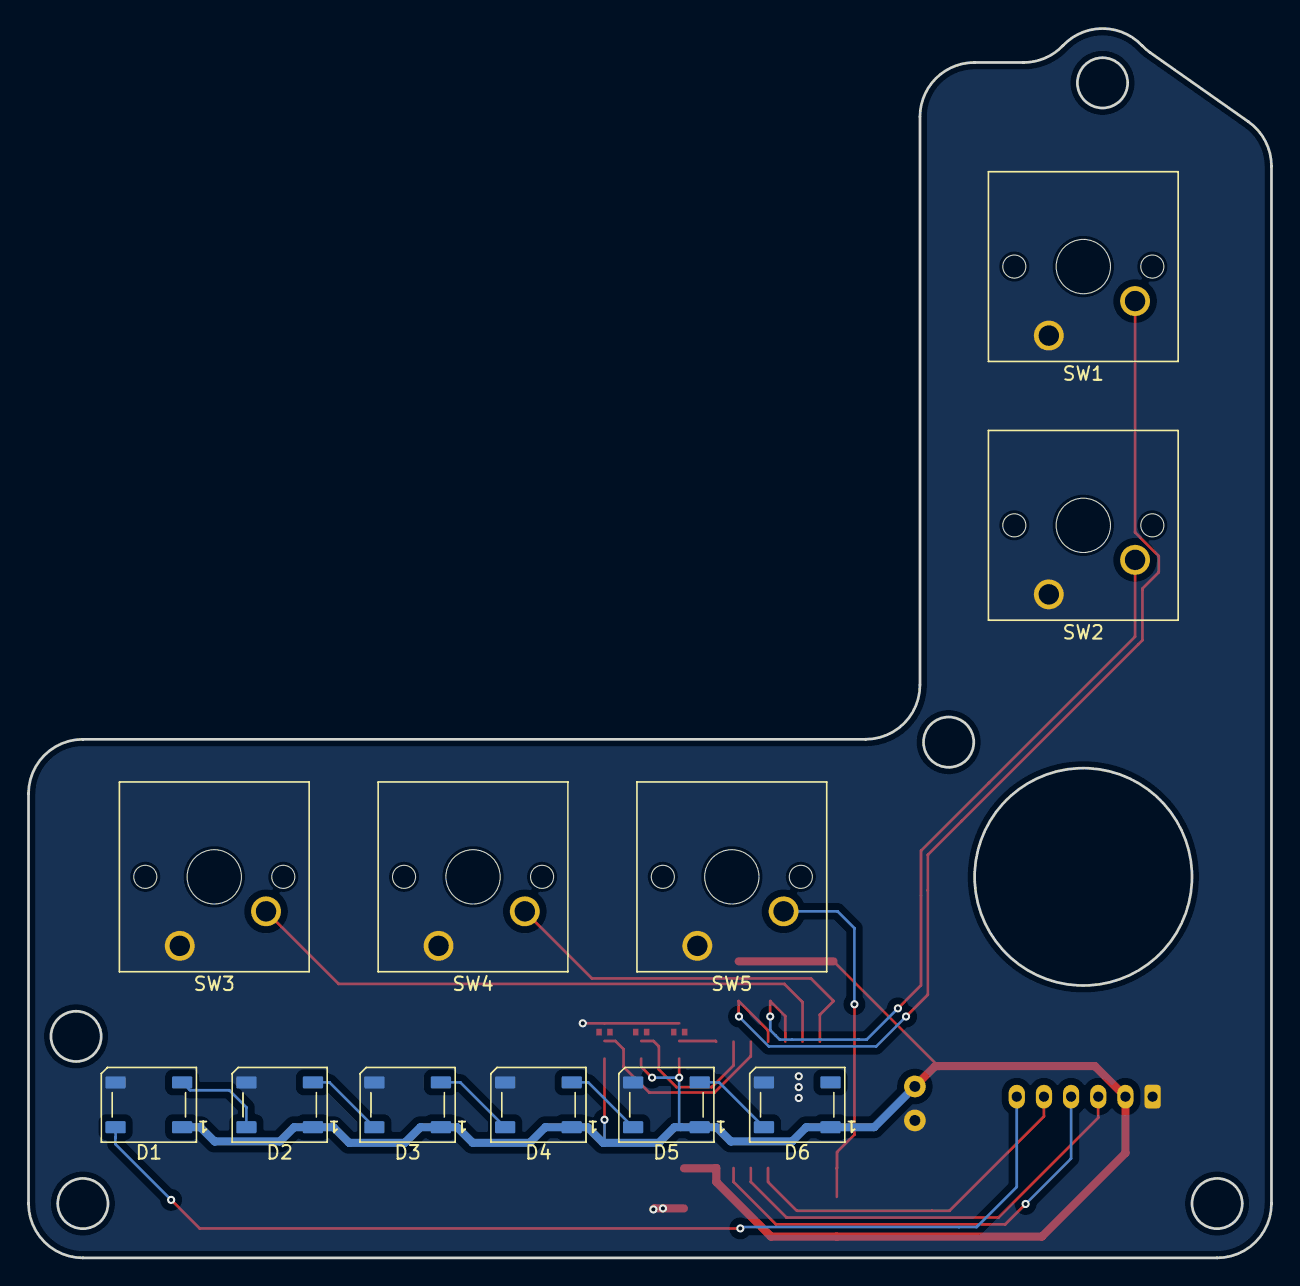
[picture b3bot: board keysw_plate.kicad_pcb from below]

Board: 2 copper layers, 91.5 x 90.5 mm, 23 parts (11 on the bottom side), 19 nets.

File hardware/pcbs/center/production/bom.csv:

Designator,Footprint,Quantity,Value,LCSC Part #
C1,C_Radial_D6.3mm_H11.0mm_P2.50mm,1,10u,
C2,1206,1,100n,
"D1, D2, D3, D4, D5, D6",LED_WS2812B_PLCC4_5.0x5.0mm_P3.2mm,6,WS2812B,
J1,JST_PH_B6B-PH-K_1x06_P2.00mm_Vertical,1,JST_PH,
"R1, R2, R3, R4, R5",1206,5,10k,
"SW1, SW2, SW3, SW4, SW5",SW_Cherry_MX_1.00u_PCB,5,SW_Push,
U1,SOIC-16W_7.5x10.3mm_P1.27mm,1,PCF8574T,

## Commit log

2025-07-23 Added journal frontmatter
2025-07-23 Updated functions image
2025-07-23 Added f3z file, removed .DS_STORE
2025-07-23 cleaned up KiCAD files
2025-07-24 updated README, split covers
